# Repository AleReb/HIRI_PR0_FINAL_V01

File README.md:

# FirmwarePro (HIRI)

Firmware para estación de monitoreo técnico-científico basada en ESP32, con adquisición de sensores, GNSS, registro en SD, telemetría HTTP y gestor de archivos por WiFi AP.

## Estado

- Plataforma objetivo: **ESP32 Dev Module** (`esp32:esp32:esp32`)
- Versión de referencia documentada: **Pro V0.1.8**

## Funcionalidades principales

- Lectura de **PMS5003** (PM1/PM2.5/PM10 + T/H según modelo)
- Lectura de **SDS198** (PM100)
- Lectura opcional de **SHT31**
- GNSS por módem SIM7600 (posición, altitud, velocidad, satélites, HDOP)
- Registro en **CSV diario** en tarjeta SD
- Envío HTTP de mediciones a backend
- UI local con OLED + 2 botones
- Modo **WiFi SD** con web manager (upload/download/rename/delete)
- Captive portal DNS para mejor compatibilidad en Windows

## Carrusel de datos persistente

En **Opciones > Configuración > Carrusel**, BTN2 abre una pantalla de control
similar a RTC. Allí **BTN2 activa/desactiva** el carrusel y **BTN1 sale**.
El estado ON/OFF se guarda en flash y se conserva al apagar o reiniciar.
Por defecto está desactivado.

Desde Serial (115200 baud, nueva línea):

```text
set carousel on
set carousel off
config display
```

Los comandos `set` guardan automáticamente con el mismo `saveConfig()` que las
demás opciones. `config` muestra también el estado, `configsave` sigue disponible
y `configreset` restaura carrusel OFF. `help` incluye la opción y sus controles.

En las vistas de datos del inicio, rota cada **10 segundos**:
**PM2.5 > temperatura > humedad**. Usa las lecturas Plantower
actuales, conservando encabezado y controles. Los puntos inferiores indican
una de las tres páginas del carrusel. Los botones mantienen la navegación habitual.
Al navegar a Empezar/Detener muestreo u Opciones, muestra la opción elegida
durante 10 segundos; si no se selecciona, vuelve a PM2.5.
Se pausa dentro de submenús, confirmaciones, WiFi, modo Full y con la OLED apagada por
inactividad. La rotación no reinicia el plazo de apagado automático. Al volver
al inicio o navegar manualmente, espera otros 10 segundos antes de cambiar.

## Reinicio manual del equipo

**Configuración > Reiniciar** y el comando Serial `reboot` utilizan el mismo
reinicio. Primero muestran el aviso durante 750 ms, sin comenzar otra tarea
AT/HTTP. Se reinicia el ESP32 y el siguiente arranque **primero verifica AT**,
registro de datos y PDP. Con una sesion previa activa prueba una conexion TCP
al host de `API_BASE`, sin enviar mediciones. Si el modem responde, conserva
su encendido y recupera red/PDP si hace falta; un fallo TCP del servidor no
provoca apagado. Si no hay AT tras la espera y se trata de reinicio manual,
recuperacion automatica, panic o watchdog, solicita el ciclo del modem con
cuenta regresiva de 30 segundos. Conserva los 5 strikes.
Los mensajes `[BOOT]` y `[MODEM]` permiten seguir cada etapa por Serial.

El reinicio manual mantiene la configuración persistente, pero deja el muestreo
apagado. El reinicio automático de recuperación conserva su restauración de
muestreo. PWRKEY/CPOF solicitan el ciclo del módem; no cortan VBAT ni permiten
verificar el apagado físico sin una señal STATUS.

El LED pulsa azul durante la animacion y las esperas AT/red/recuperacion,
tambien dentro de TinyGSM, con la misma secuencia tras reinicio y encendido.
Respeta `set led off`. Al entrar al loop vuelve al color de PM2.5.
En un reset que conserva el modem se omite la descarga XTRA inicial para
no sumar otra espera de hasta 120 segundos. La prueba TCP confirma acceso
al servidor consultado; un fallo no distingue caida del servidor de falta
de ruta a internet.

## Configurar equipos y sensores de la API

En `HIRI_PR0_FINAL_V01.ino`, cambie solamente `DEVICE_ID_STR` para seleccionar
un equipo de `DEVICE_API_PROFILES`. La tabla permanece junto a `API_BASE`,
en el lugar de las listas originales, con todos los equipos visibles.
La URL utiliza los IDs de sensores, variables y valores del perfil elegido.
`"06"` y `"6"` seleccionan el mismo perfil; el identificador escrito se conserva
en pantalla, archivos y valor enviado del equipo.

Para agregar un equipo, copie una fila de la tabla y complete:

- ID del equipo.
- Lista de IDs de sensores asignados por el backend.
- Lista de variables: base, SHT31 o SDS198.
- Sensor extra: `EXTRA_NONE`, `EXTRA_SHT31` o `EXTRA_SDS198`.

El orden de las mediciones está comentado encima de la tabla. Las tres listas
(sensores, variables y valores) deben tener la misma cantidad de campos.
Si el ID no existe o las cantidades no coinciden, el firmware rechaza el
envío HTTP y deja un mensaje en Serial; los sensores y la pantalla continúan.
Los IDs del backend son explícitos: no se deducen del número de equipo.

Para un tipo de sensor nuevo, agregue su opción a `ExtraSensorApi`, su lista
de variables y los valores correspondientes en `buildMeasurementUrl()`.
La inicialización y lectura del hardware se agregan en `setup()`/`loop()`;
la tabla configura la telemetría y conserva los drivers actuales.

### Lista de dispositivos HIRI

Perfiles disponibles en `DEVICE_API_PROFILES`: **1–10 y 80–89**.
Los HIRI **82 y 83** ya estaban registrados y coinciden con los mapeos
proporcionados; se agregaron **84, 85, 86, 87, 88 y 89**. Cada uno utiliza
19 valores y el perfil `EXTRA_SHT31`. HIRI 86 tiene una sola entrada.

| HIRI / DEVICE_ID_STR | PMS, campos 1–5 | Módem/GPS, 6–10 | RTC, 11 | Batería, 12 | Equipo, 13–17 | SHT31, 18–19 |
|---|---|---|---|---|---|---|
| 82 | 939 | 940 | 941 | 942 | 943 | 944 |
| 83 | 945 | 946 | 947 | 948 | 949 | 950 |
| 84 | 951 | 952 | 953 | 954 | 955 | 956 |
| 85 | 957 | 958 | 959 | 960 | 961 | 962 |
| 86 | 963 | 964 | 965 | 966 | 967 | 968 |
| 87 | 969 | 970 | 971 | 972 | 973 | 974 |
| 88 | 975 | 976 | 977 | 978 | 979 | 980 |
| 89 | 981 | 982 | 983 | 984 | 985 | 986 |

Cada ID de la tabla se repite para todos los campos de su grupo. Por ejemplo,
HIRI 84 utiliza cinco veces 951 para PMS, cinco veces 952 para módem/GPS,
953 para RTC, 954 para batería, cinco veces 955 para equipo y dos veces 956
para SHT31. El firmware mantiene las listas completas y explícitas.

El orden de `idsVariables` es común a estos ocho equipos:

```text
3,6,7,8,9,11,12,15,45,46,3,4,11,12,42,43,44,3,6
```

| Posición | Grupo | ID variable | Valor enviado | Unidad |
|---|---|---|---|---|
| 1 | PMS | 3 | Temperatura | °C |
| 2 | PMS | 6 | Humedad | % |
| 3 | PMS | 7 | PM1.0 | µg/m³ |
| 4 | PMS | 8 | PM2.5 | µg/m³ |
| 5 | PMS | 9 | PM10 | µg/m³ |
| 6 | Módem/GPS | 11 | Latitud | ° |
| 7 | Módem/GPS | 12 | Longitud | ° |
| 8 | Módem/GPS | 15 | Intensidad de señal telefónica | Adimensional |
| 9 | Módem/GPS | 45 | Velocidad | km/h |
| 10 | Módem/GPS | 46 | Satélites | Entero |
| 11 | RTC | 3 | Temperatura interna | °C |
| 12 | Batería | 4 | Voltaje | V |
| 13 | Equipo | 11 | Latitud | ° |
| 14 | Equipo | 12 | Longitud | ° |
| 15 | Equipo | 42 | Identificador DEVICE_ID_STR | String |
| 16 | Equipo | 43 | Número de envíos | Numeral |
| 17 | Equipo | 44 | Registro SD activo | Bool (0/1) |
| 18 | SHT31 | 3 | Temperatura | °C |
| 19 | SHT31 | 6 | Humedad | % |

Para seleccionar uno, cambie solamente el identificador, por ejemplo:

```cpp
const char *DEVICE_ID_STR = "89";
```

Los textos descriptivos de `valores` proporcionados representan el significado
de cada campo. El firmware los sustituye por las lecturas actuales al construir
la URL de `insertarMedicion`, usando el endpoint definido en `API_BASE`.

## Arranque y recuperación sin conexión

Debajo de `VERSION`, en `HIRI_PR0_FINAL_V01.ino`, configure:

```cpp
const uint8_t CONNECTION_MAX_STRIKES = 5;
```

Antes de pulsar PWRKEY se consulta AT durante hasta 15 segundos, porque un
reinicio del ESP32 puede dejar el módem encendido. Si no responde, se aplica
el pulso de la placa y se permiten 5 strikes de 15 segundos cada uno.
PWRKEY se vuelve a pulsar solo cada 3 strikes sin respuesta, dejando unos
45 segundos entre pulsos. Esto conserva los reintentos del original y permite
completar el arranque de la UART. La etapa AT puede tardar unos 90 segundos.

El registro celular permite 5 intentos de hasta 60 segundos, como la espera
por intento del firmware antiguo. PDP agrega los tiempos internos de TinyGSM
(hasta 60 s de NETCLOSE y 75 s de NETOPEN, además de otros comandos).
Por eso el arranque sin red puede tardar varios minutos. Una vez agotados los
intentos, se pasa al modo normal para leer y mostrar datos. Sin AT se omiten
GNSS y HTTP; con AT pero sin internet, GNSS se inicia y se omite XTRA.

En el loop se consulta PDP cada minuto. Tras **30 minutos continuos sin PDP**,
se guardan contadores, archivo CSV y estados HTTP/SD, y se reinicia el ESP32.
Ese arranque comprueba primero AT y PDP; conserva un módem que responde.
Solo si AT no responde tras esperar solicita apagarlo/encenderlo y espera
30 segundos para completar el apagado. Se restaura el muestreo que
estaba activo; SD se restaura solamente si se monta correctamente. La marca de
recuperación es de un solo uso y solo se aplica a ese reinicio por software.

Recuperar PDP reinicia el contador de desconexión. Un error HTTP del servidor
no provoca reinicio si PDP sigue activo. Durante WiFi SD no se reinicia el
equipo: al salir se dispone de otros 30 minutos. El plazo se ajusta mediante
`NETWORK_REBOOT_AFTER_MS`, junto a la versión.

HTTP hace un intento de reconexión PDP por llamada y espera al menos 60 segundos
tras un fallo. El watchdog es de 180 segundos para permitir que TinyGSM termine;
la llamada PDP sigue siendo bloqueante y puede pausar la UI mientras espera.

La polaridad GPIO4 HIGH/LOW se conserva de la placa actual. PWRKEY es una
solicitud de encendido/apagado, no un corte de alimentación. Sin STATUS ni
control de VBAT no se puede verificar un apagado físico. Referencia de tiempos:
[SIMCom SIM7600 Hardware Design, sección 3.2](https://media.digikey.com/pdf/Data%20Sheets/SIMCom%20PDFs/SIM7600_Series_Hardware_Design.pdf).

## Documentación

- **Manual de Usuario:** `documentacion/MANUAL_USUARIO.md`
- **Manual Técnico:** `documentacion/MANUAL_TECNICO.md`
- **PCB, pinout y revisión de hardware:** [`PCB/README.md`](PCB/README.md)
- **Historial de cambios:** `documentacion/CAMBIOS.md`
- **Guía de desarrollo/versionado:** `documentacion/DEVELOPER_GUIDELINES.md`
- **Estructura de menú:** `documentacion/menu_structure.md`
- **Licencia:** `LICENSE`

## Test independiente de componentes

El repositorio incluye el sketch
[`test_componentes/test_componentes.ino`](test_componentes/test_componentes.ino),
diseñado para revisar el hardware básico antes de cargar el firmware completo.
Esta prueba funciona de manera independiente y no inicia el módem, GNSS, WiFi,
tarjeta SD, SDS198 ni los servicios de telemetría.

### Componentes revisados

| Componente | Conexión usada | Prueba realizada |
|---|---|---|
| OLED SSD1306 128×64 | I²C `0x3C`, SDA 21, SCL 22 | Detección I²C, patrón visual y pantalla de estado |
| RTC DS3231 | I²C `0x68` | Presencia, hora, temperatura interna y pérdida de alimentación |
| SHT41 | I²C `0x44` | Detección, número de serie, temperatura y humedad en pantalla dedicada |
| Plantower/PMS | 9600 baud, RX 5, TX 18 | Trama, checksum, PM1, PM2.5, PM10 y T/H cuando el modelo las incluye |
| NeoPixel RGB | GPIO 12 | Secuencia rojo, verde, azul, blanco y apagado |
| Botón 1 | GPIO 19, activo en HIGH | Estado, antirrebote y contador de pulsaciones |
| Botón 2 | GPIO 23, activo en HIGH | Estado, antirrebote y contador de pulsaciones |
| Batería | ADC GPIO 35 | Promedio filtrado y voltaje calibrado |

Los botones utilizan las resistencias pull-down externas de la placa. Por eso se
configuran como `INPUT`: sueltos se leen en LOW y pulsados en HIGH.

### Información mostrada

La OLED utiliza el mismo constructor SSD1306, fuente y rotación `U8G2_R2` del
firmware principal. Al arrancar muestra un patrón de pantalla y luego alterna
cada cinco segundos entre el resumen general y una pantalla dedicada al SHT41.
El resumen es similar al siguiente:

```text
TEST COMPONENTES HIRI
O:3C R:OK 12:34:56
PMS:1/25/10 5/12/18
PMS T/H:23.4C 45.2%
RGB:VERDE BAT:4.08V
B1:UP #0    B2:UP #0
```

- `PMS:ESPERANDO` indica que todavía no llegó una trama.
- `PMS:SIN DATOS/FAIL` indica ausencia de tramas válidas o pérdida de datos.
- `PMS T/H:NO DISP.` indica que el Plantower transmite partículas, pero su
  modelo no incluye temperatura y humedad válidas.
- `R:BAT!` indica que el RTC responde, pero registró una pérdida de alimentación
  y su hora podría ser incorrecta. El test nunca modifica la hora del RTC.
- `B1` y `B2` muestran `UP` al soltar, `DOWN` al pulsar y el total de
  pulsaciones válidas.

El monitor serie a **115200 baud** entrega además el escaneo I²C, cada trama
válida del Plantower, errores de checksum, hora y temperatura del RTC, cambios
del RGB, pulsaciones y voltaje de batería.

El encabezado cambia a `TEST: TODO OK*` cuando OLED, RTC, SHT41, Plantower,
batería y ambos botones superan las verificaciones automáticas. Para la batería se acepta
como rango diagnóstico de una celda conectada entre 2,50 V y 4,50 V. El
asterisco recuerda que el RGB debe comprobarse visualmente: el ESP32 puede
ordenar un color, pero no medir si el LED realmente emitió luz.

### Controles del test

- **BTN1:** avanza manualmente al siguiente color del NeoPixel.
- **BTN2:** activa o desactiva el recorrido automático de colores.

### Uso del test

1. Abra `test_componentes/test_componentes.ino` en Arduino IDE.
2. Seleccione **ESP32 Dev Module**.
3. Use las dependencias incluidas en [`libraries`](libraries/README.md).
4. Cargue el sketch y abra el monitor serie a **115200 baud**.
5. Revise el patrón OLED, los colores y los valores mostrados.
6. Pulse ambos botones al menos una vez y confirme que sus estados y contadores
   cambien correctamente.

Con Arduino CLI, la ruta de librerías debe indicarse explícitamente:

```powershell
arduino-cli compile --fqbn esp32:esp32:esp32 --libraries .\libraries .\test_componentes
```

## Compilación y carga (Arduino CLI)

Las dependencias externas están consolidadas en `libraries/`. Consulte
[`libraries/README.md`](libraries/README.md) para ver versiones y licencias.

### Compilar

```bash
arduino-cli compile --fqbn esp32:esp32:esp32 --libraries ./libraries .
```

### Subir a dispositivo (ejemplo COM5)

```bash
arduino-cli upload -p COM5 --fqbn esp32:esp32:esp32 FirmwarePro.ino
```

## Disclaimer de responsabilidad

Este proyecto se entrega **"tal cual"** (as-is), sin garantías explícitas ni implícitas de funcionamiento, disponibilidad o aptitud para un propósito específico.

El despliegue en terreno, la seguridad del sistema, la validación de datos y el cumplimiento normativo son responsabilidad del usuario/integrador.

Los autores y colaboradores no se responsabilizan por pérdidas de datos, daños directos o indirectos ni por uso fuera de contexto técnico seguro.

## Licencia de documentación

La documentación de este repositorio se publica bajo:

**Creative Commons Attribution-NonCommercial 4.0 International (CC BY-NC 4.0)**  
https://creativecommons.org/licenses/by-nc/4.0/

- ✅ Se permite compartir y adaptar con atribución.
- ❌ No se permite uso comercial sin autorización adicional.

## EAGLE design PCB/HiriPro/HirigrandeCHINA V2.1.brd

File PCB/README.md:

# Hardware PCB de HIRI Pro

Esta carpeta contiene la placa portadora (*carrier board*) correspondiente al
firmware principal [`HIRI_PR0_FINAL_V01.ino`](../HIRI_PR0_FINAL_V01.ino). El
diseño aloja el módulo ESP32/SIM7600 mediante dos hileras de 15 pines y distribuye
alimentación y señales hacia el sensor Plantower, pantalla, RTC, LED RGB y dos
botones.

> **Estado de la revisión (19-08-2026): no enviar todavía a fabricación.** El
> archivo de placa contiene cuatro conexiones sin rutear en `3V3`; además, deben
> resolverse las observaciones de compatibilidad con el firmware indicadas más
> abajo y ejecutar ERC/DRC en EAGLE.

## Archivos del diseño

| Archivo | Contenido |
|---|---|
| [`HiriPro/HirigrandeCHINA V2.1.sch`](HiriPro/HirigrandeCHINA%20V2.1.sch) | Esquemático eléctrico |
| [`HiriPro/HirigrandeCHINA V2.1.brd`](HiriPro/HirigrandeCHINA%20V2.1.brd) | Layout de la PCB |

Los dos archivos son XML de **Autodesk EAGLE 9.6.2**. El repositorio no incluye
Gerbers, archivos de perforado, *pick and place* ni BOM de fabricación; estos
deben exportarse únicamente después de cerrar la revisión eléctrica y el DRC.

## Bloques de hardware

- `JP1` y `JP2`: cabezales 1x15 del módulo ESP32/SIM7600.
- `XA1`: conector Molex 53048-0810 de ocho posiciones para Plantower/PMS.
- `STEPUP`: cabecera de tres pines para elevador `VBAT` a `5V`.
- `RTC`: conector JST-XH de cinco posiciones para DS3231.
- `SCREEN`: conector JST-SH para la pantalla OLED I²C.
- `I2C`: conector JST-SH de expansión I²C; permite conectar, por ejemplo, el
  SHT31 utilizado opcionalmente por el firmware.
- `RGB`: conector JST-SH para NeoPixel externo.
- `U$1` y `U$2`: pulsadores Cherry MX, con resistencias pull-down de 10 kΩ.
- `C1` a `C10`: posiciones SMC_D para condensadores polarizados. Sus valores no
  están definidos en el esquemático y deben completarse antes de generar la BOM.

La PCB es de dos capas: `Top` y `Bottom`. Las reglas guardadas especifican pista
mínima de 0,4 mm, perforación mínima de 0,35 mm y separación pista-pista de
0,3 mm. Estos valores describen el archivo, pero no sustituyen la comprobación
contra las capacidades del fabricante elegido.

## Pinout y relación con el firmware

### Señales principales del ESP32

| Función | GPIO efectivo | Red o conexión PCB | Definición en firmware | Revisión |
|---|---:|---|---|---|
| Módem RX | 26 | Pin del módulo en `JP1` | `MODEM_RX` | Coincide |
| Módem TX | 27 | Pin del módulo en `JP1` | `MODEM_TX` | Coincide |
| Módem PWRKEY | 4 | Pin del módulo en `JP1` | `MODEM_PWRKEY` | Coincide |
| Módem DTR | 32 | Pin del módulo en `JP1` | `MODEM_DTR` | Coincide |
| Módem FLIGHT | 25 | Pin del módulo en `JP1` | `MODEM_FLIGHT` | Coincide |
| PMS: recepción del ESP32 | 5 | `JP2.7` (`RX2`) ↔ `XA1.5` | Uso efectivo de `SoftwareSerial` | Coincide, pero los nombres de macros inducen a error |
| PMS: transmisión del ESP32 | 18 | `JP2.6` (`TX2`) ↔ `XA1.4` | Uso efectivo de `SoftwareSerial` | Coincide, pero los nombres de macros inducen a error |
| I²C SDA | 21 | `JP2.10`, `RTC.4`, `SCREEN.1`, `I2C.1` | `Wire` por defecto | Coincide |
| I²C SCL | 22 | `JP2.11`, `RTC.3`, `SCREEN.2`, `I2C.2` | `Wire` por defecto | Coincide |
| NeoPixel | 12 | `JP1.14` (`RGB`) ↔ `RGB.1` | `NEOPIX_PIN` | Coincide |
| Botón 1 | 19 | `JP2.9` (`BOT1`) | `BUTTON_PIN_1` | GPIO coincide; lógica eléctrica por corregir |
| Botón 2 | 23 | `JP2.8` (`BOT2`) | `BUTTON_PIN_2` | GPIO coincide; lógica eléctrica por corregir |
| SD SCLK | 14 | Pin del módulo en `JP1` | `SD_SCLK` | Coincide |
| SD MISO | 2 | Pin del módulo en `JP1` | `SD_MISO` | Coincide |
| SD MOSI | 15 | Pin del módulo en `JP1` | `SD_MOSI` | Coincide |
| SD CS | 13 | Pin del módulo en `JP1` | `SD_CS` | Coincide |
| Medición de batería | 35 | Sensado propio del módulo | `BAT_PIN` | No está implementado como una red separada en esta carrier |
| SDS198 RX | 39 | Conexión externa al módulo | `Serial2.begin(..., 39, -1)` | No existe conector dedicado en esta PCB |

En [`config.h`](../config.h), las macros del PMS se llaman `pms_RX=18` y
`pms_TX=5`, pero el objeto se construye en orden invertido:
`SoftwareSerial pms(pms_TX, pms_RX)`. Por eso la configuración efectiva del
ESP32 es **RX=GPIO5 y TX=GPIO18**, que es la que debe usarse al comprobar la
placa. Conviene renombrar esas macros en una futura revisión para eliminar la
ambigüedad.

`POWER_PIN` está definido como GPIO33, pero su uso se encuentra comentado en el
firmware principal. La red GPIO33 de la placa no controla actualmente una carga
desde el programa.

### Conectores periféricos

Las referencias siguientes usan el número de pad guardado en EAGLE. Antes de
armar cables, confirme también la orientación del conector y la marca de pin 1
en la vista de placa.

| Conector | Pad | Señal |
|---|---:|---|
| `XA1` Plantower | 8 | `5V`, salida del step-up |
|  | 7 | `GND` |
|  | 6 | `SET`, sin conexión al ESP32 |
|  | 5 | `RX2`; datos del sensor hacia RX del ESP32 (GPIO5) |
|  | 4 | `TX2`; datos del ESP32 (GPIO18) hacia RX del sensor |
|  | 1–3 | Sin conexión |
| `RTC` | 1 | `GND` |
|  | 2 | Sin conexión |
|  | 3 | `SCL` |
|  | 4 | `SDA` |
|  | 5 | `3V3` |
| `SCREEN` | 1 | `SDA` |
|  | 2 | `SCL` |
|  | 3 | `GND` |
|  | 4 | `VBAT` |
|  | 5–6 | Blindaje a `GND` |
| `I2C` | 1 | `SDA` |
|  | 2 | `SCL` |
|  | 3 | `GND` |
|  | 4 | `VBAT` |
|  | 5–6 | Blindaje a `GND` |
| `RGB` | 1 | Datos, GPIO12 |
|  | 2 | `GND` |
|  | 3 | `VBAT` |
|  | S1–S2 | Blindaje a `GND` |
| `STEPUP` | 1 | Entrada `VBAT` |
|  | 2 | `GND` |
|  | 3 | Salida `5V` hacia `XA1.8` |

**Atención:** `SCREEN`, `I2C` y `RGB` reciben `VBAT`, no `3V3` regulados. Antes
de conectar un módulo, compruebe su rango de alimentación y el voltaje máximo de
la batería. Las líneas lógicas del ESP32 siguen siendo de 3,3 V.

## Hallazgos pendientes

### 1. Cuatro conexiones `3V3` sin rutear

El `.brd` conserva cuatro segmentos en la capa EAGLE `19 Unrouted`, todos en la
red `3V3`:

| Desde (mm) | Hasta (mm) |
|---|---|
| `(48.625, 19.625)` | `(48.625, 19.6893)` |
| `(48.750, 10.175)` | `(48.750, 10.2500)` |
| `(34.450, 14.900)` | `(34.425, 14.9500)` |
| `(34.600, 19.625)` | `(34.500, 19.5250)` |

Aunque son segmentos muy cortos, EAGLE todavía los considera *airwires*. Se
deben rutear o resolver mediante el plano de cobre y luego ejecutar `RATSNEST`
hasta obtener **0 unrouted**.

### 2. Lógica de botones incompatible

En el esquemático, cada pulsador conecta su señal a `3V3` y tiene una resistencia
externa de 10 kΩ a `GND`: queda suelto en LOW y pulsado en HIGH. Sin embargo, el
firmware principal configura ambos GPIO como `INPUT_PULLUP` y atiende el flanco
`FALLING`. Esto puede registrar la liberación en vez de la pulsación y enfrenta
el pull-up interno con el pull-down externo.

Debe elegirse y probarse una solución antes de liberar hardware/firmware:

- conservar la PCB y usar entradas normales o pull-down, con interrupción
  `RISING`; o
- conservar la lógica activa en LOW del firmware y modificar el circuito para
  que el pulsador conecte a GND con pull-up.

El sketch [`test_componentes/test_componentes.ino`](../test_componentes/test_componentes.ino)
ya prueba la primera topología: entradas activas en HIGH con los pull-down de la
placa.

### 3. BOM incompleta

`C1` a `C10` usan encapsulado polarizado SMC_D, pero no tienen capacitancia ni
tensión nominal asignadas. También debe registrarse el modelo exacto del módulo
step-up. No sustituya componentes ni genere una orden de montaje hasta definir
estos datos y verificar polaridades.

### 4. Periféricos que no tienen conector dedicado

El firmware lee un SDS198 por GPIO39 y puede leer un SHT31 en `0x44`. La carrier
no ofrece un conector rotulado para SDS198; el SHT31 puede compartir `I2C`, pero
el conector lo alimenta desde `VBAT`. Estas conexiones deben quedar definidas en
el mazo de cables y en la matriz de versión del equipo.

## Procedimiento de validación recomendado

1. Abrir juntos el `.sch` y el `.brd` en EAGLE 9.6.2 o una versión compatible.
2. Completar valores y números de parte de la BOM.
3. Resolver las cuatro conexiones `3V3` y confirmar `RATSNEST: 0 unrouted`.
4. Ejecutar ERC sobre el esquemático y DRC sobre la placa usando las reglas del
   fabricante; documentar todas las excepciones.
5. Resolver la topología de los botones y sincronizarla con el firmware.
6. Verificar orientación y continuidad de cada conector con un multímetro, sin
   insertar todavía el ESP32 ni los sensores.
7. Alimentar con fuente limitada en corriente y comprobar `VBAT`, `3V3` y la
   salida `5V` del step-up.
8. Insertar el módulo y ejecutar el
   [`test_componentes`](../test_componentes/README.md) antes del firmware completo.
9. Validar OLED, RTC, PMS, RGB, botones y batería; después probar SD, módem,
   GNSS, SDS198 y telemetría con el firmware principal.
10. Solo entonces exportar Gerbers/Excellon y revisar visualmente cada capa,
    máscara, serigrafía, contorno y perforación.

## Trazabilidad

El nombre del diseño indica revisión de hardware **V2.1**. La versión del
firmware se mantiene por separado en la constante `VERSION`. Para cada lote se
recomienda registrar como mínimo: revisión de PCB, commit del repositorio,
versión de firmware, BOM aprobada, fabricante y fecha de montaje.

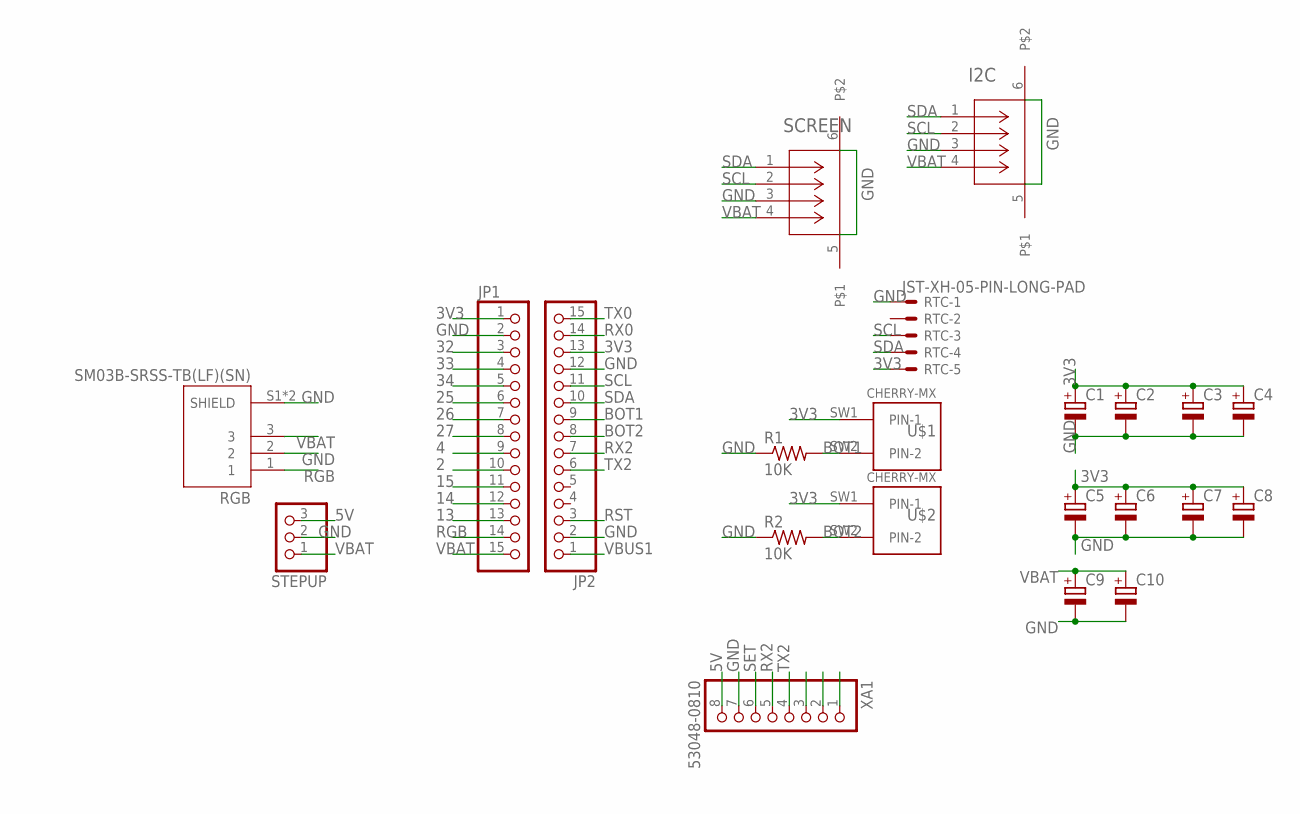
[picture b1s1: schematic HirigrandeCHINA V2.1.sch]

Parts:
C1, C2, C3, C4, C5, C6, C7, C8, C9, C10: CPOL-EUSMCD; SMC_D
I2C: SM04B-SRSS-TB; CONN_SM04B-SRSS-TB_JST
JP1, JP2: PINHD-1X15; 1X15
R1, R2: 10K; 0204/7
RGB: SM03B-SRSS-TB(LF)(SN); JST_SM03B-SRSS-TB(LF)(SN)
RTC: JST-XH-05-PIN-LONG-PAD; JST-XH-05-PACKAGE-LONG-PAD
SCREEN: SM04B-SRSS-TB; CONN_SM04B-SRSS-TB_JST
STEPUP: PINHD-1X3; 1X03
U$1, U$2: CHERRY-MX
XA1: 53048-0810; MOLEX_53048-0810

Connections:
2: JP1.10
3V3: C1.+, C2.+, C3.+, C4.+, C5.+, C6.+, C7.+, C8.+, JP1.1, JP2.13, RTC.5, U$1.SW1 (PIN-1), U$2.SW1 (PIN-1)
4: JP1.9
5V: STEPUP.3, XA1.8
13: JP1.13
14: JP1.12
15: JP1.11
25: JP1.6
26: JP1.7
27: JP1.8
32: JP1.3
33: JP1.4
34: JP1.5
BOT1: JP2.9, R1.2, U$1.SW2 (PIN-2)
BOT2: JP2.8, R2.2, U$2.SW2 (PIN-2)
GND: C1.-, C2.-, C3.-, C4.-, C5.-, C6.-, C7.-, C8.-, C9.-, C10.-, I2C.3, I2C.5, I2C.6, JP1.2, JP2.2, JP2.12, R1.1, R2.1, RGB.2, RGB.S1 (SHIELD), RGB.S2 (SHIELD), RTC.1, SCREEN.3, SCREEN.5, SCREEN.6, STEPUP.2, XA1.7
RGB: JP1.14, RGB.1
RST: JP2.3
RX0: JP2.14
RX2: JP2.7, XA1.5
SCL: I2C.2, JP2.11, RTC.3, SCREEN.2
SDA: I2C.1, JP2.10, RTC.4, SCREEN.1
SET: XA1.6
TX0: JP2.15
TX2: JP2.6, XA1.4
VBAT: C9.+, C10.+, I2C.4, JP1.15, RGB.3, SCREEN.4, STEPUP.1
VBUS1: JP2.1

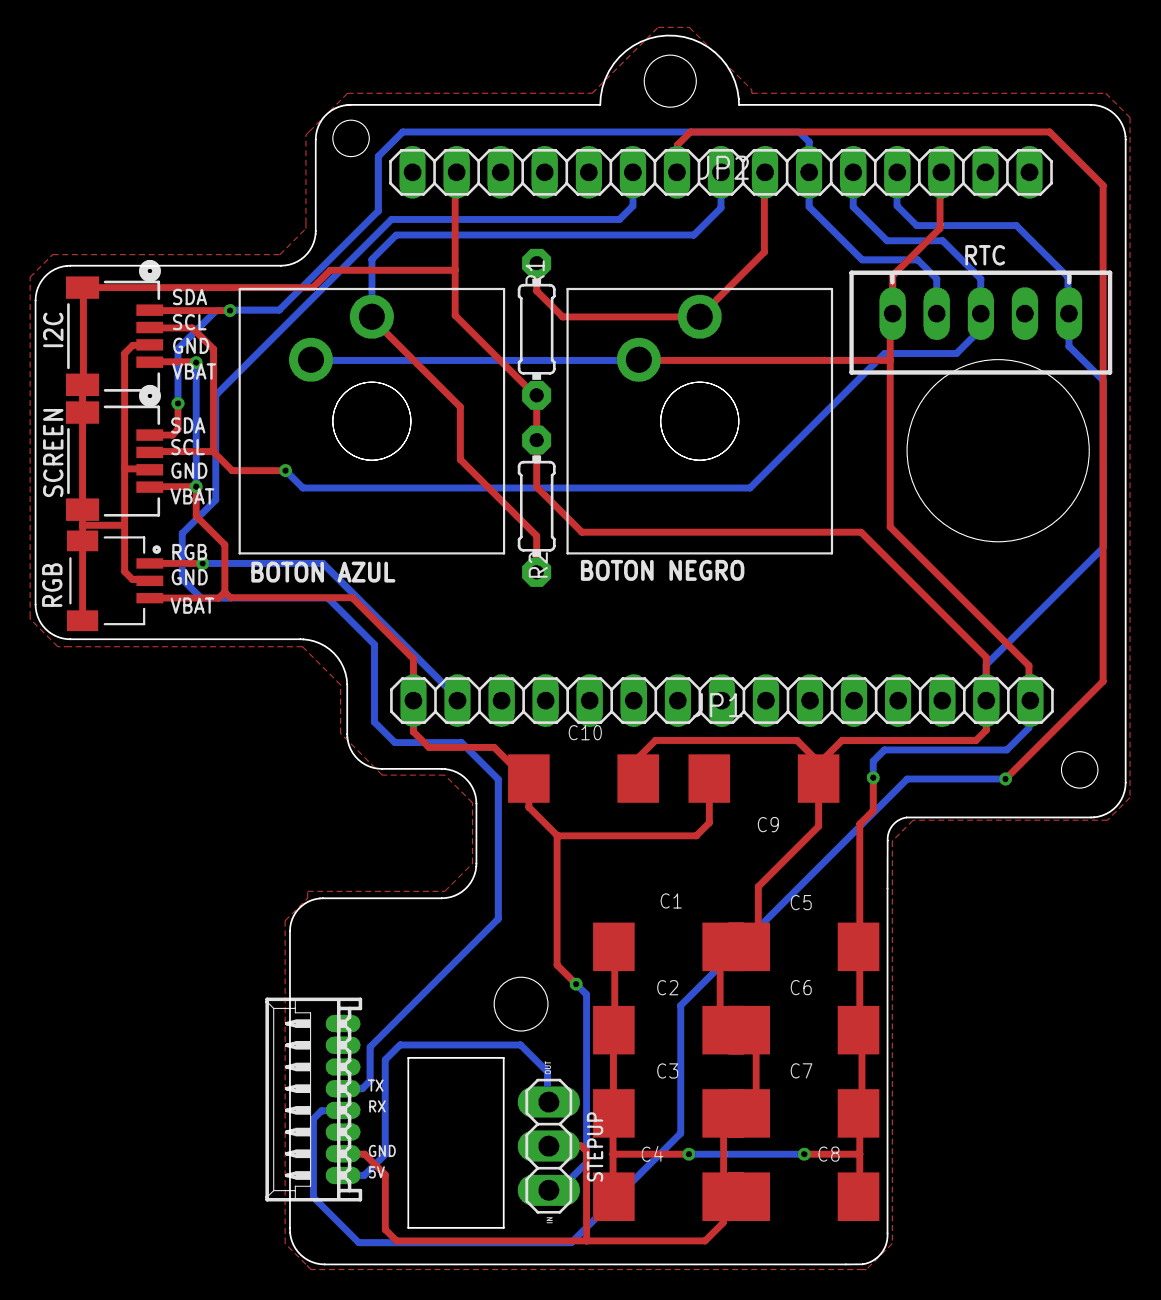
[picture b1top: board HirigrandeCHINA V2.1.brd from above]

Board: 2 copper layers, 62.8 x 70.8 mm, 22 parts (0 on the bottom side), 11 nets.
